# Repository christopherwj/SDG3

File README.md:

# SDG3 - Powered Speaker System - Happy Tunes

## What should I expect to find in this repo?

Here you can find all of the files related to Team 3's Senior Design Project

This includes: components, datasheets, simulations, source code and more!

## Who is on the team?

| Team Member         | Field               |
| :------------------ | :------------------ |
| Brian Ahlers        | Electrical Engineer |
| Abraham Carranza    | Computer Engineer   |
| Kaitlyn Hamiter     | Electrical Engineer |
| Christopher Johnson | Computer Engineer   |
| Christopher Kihano  | Computer Engineer   |

# Shortcuts

From here on you will find sections detailing different points of Team 3's progress, links to documents and Google Drive directories.

## Senior Design B

### Draw.io Diagrams

- <a href="https://drive.google.com/drive/folders/15kxVudf5h-fhxRucdEdU0__9-gUpvDf6?usp=sharing" target="_blank">Folder Directory</a>

### System Integration Testing
- [Report](https://docs.google.com/document/d/11B_BZgX_fD9LDzKS0TlejT2W-SY3xGZJBUBTwWxWOKQ/edit?usp=sharing)
- [Folder Directory](https://drive.google.com/drive/folders/19PX26QaqbOIaYj3eWc8ziYZd34B6GGTo?usp=sharing)

### Hardware Readiness

- [Report](https://docs.google.com/document/d/16WcHxM67mR_bLpcuLu_cNokmKFwlc5yR9lt_XE9QbTI/edit?usp=sharing)
- [Folder Directory](https://drive.google.com/drive/folders/1j9h-cdcIw9vPNtkVY1A0dE3LBrUp3cXq?usp=sharing)

### Firmware Readiness

- [Report](https://docs.google.com/document/d/1_yuX03Fo50LZgdDcOuhRRBqLqM6c0yxrTySWzuhtTM4/edit?usp=sharing)
- [Folder Directory](https://drive.google.com/drive/folders/1t-pBYhPXyJxyrI6B_gw4tiY_lfn7Jp15?usp=sharing)

### Team Labor Hours

- [Spreadsheet](https://docs.google.com/spreadsheets/d/12QhF0Mqp7NLQ3RBZjQvClqkk2QXMBvIy/edit?usp=sharing&ouid=104676273414826873055&rtpof=true&sd=true)
- [Folder Directory](https://drive.google.com/drive/folders/19Oa_INHHnQHptVcXvDggzD6vj_AUFLqU?usp=sharing)

## Senior Design A

### Draw.io Diagrams
- <a href="https://drive.google.com/drive/folders/15kxVudf5h-fhxRucdEdU0__9-gUpvDf6?usp=sharing" target="_blank">Folder Directory</a>

### System Description, Requirements, Validation

- [Report](https://docs.google.com/document/d/1fnrOCIRyJVDsxmta0oakdDbBKZW54d827w0m6OqQ11Q/edit?usp=sharing)
- [Folder Directory](https://drive.google.com/drive/folders/1NczNZ4O1j9Vx4oX85sgfJVTjJTQ-W3sH?usp=sharing)

### Risk Analysis

- [Report](https://drive.google.com/file/d/1sAik6q6ureZYssgTLGljBEHL8I2Zk15t/view?usp=sharing)
- [Folder Directory](https://drive.google.com/drive/folders/1NczNZ4O1j9Vx4oX85sgfJVTjJTQ-W3sH?usp=sharing)

### Prototype Activity

- [Report](https://drive.google.com/file/d/1stdICW6GUIWn7OOhUiIIFrHZ0VR0cqvk/view?usp=sharing)
- [Folder Directory](https://drive.google.com/drive/folders/1NczNZ4O1j9Vx4oX85sgfJVTjJTQ-W3sH?usp=sharing)

### Critical Design Review

- [Report](https://docs.google.com/presentation/d/1inkozGnM1z5_KCovr3mFNu3Ky42EYbz6ArtEo2gSImo/edit?usp=sharing)
- [Folder Directory](https://drive.google.com/drive/folders/1jWTyNvOkjsP8tEsv12XOycAalzhh8IQb?usp=sharing)

### Final Report

- [Report](https://docs.google.com/document/d/1AqZGzt35glmXr1-TCmBBXokeJKedO_IO3BRvOg3bReY/edit?usp=sharing)
- [Folder Directory](https://drive.google.com/drive/folders/1KJQUjUjOi4YFd6RUpi_W71EKjcTsQYTU?usp=sharing)

### Team Labor Hours

- [Spreadsheet](https://docs.google.com/spreadsheets/d/1y0pf061RG8TchD4RHMXZIr2CGgnv92BU/edit?usp=sharing&ouid=104676273414826873055&rtpof=true&sd=true)
- [Folder Directory](https://drive.google.com/drive/folders/1Dg6yo43kKn5nfYz5vgzlIPh3S6AtKxnr?usp=sharing)

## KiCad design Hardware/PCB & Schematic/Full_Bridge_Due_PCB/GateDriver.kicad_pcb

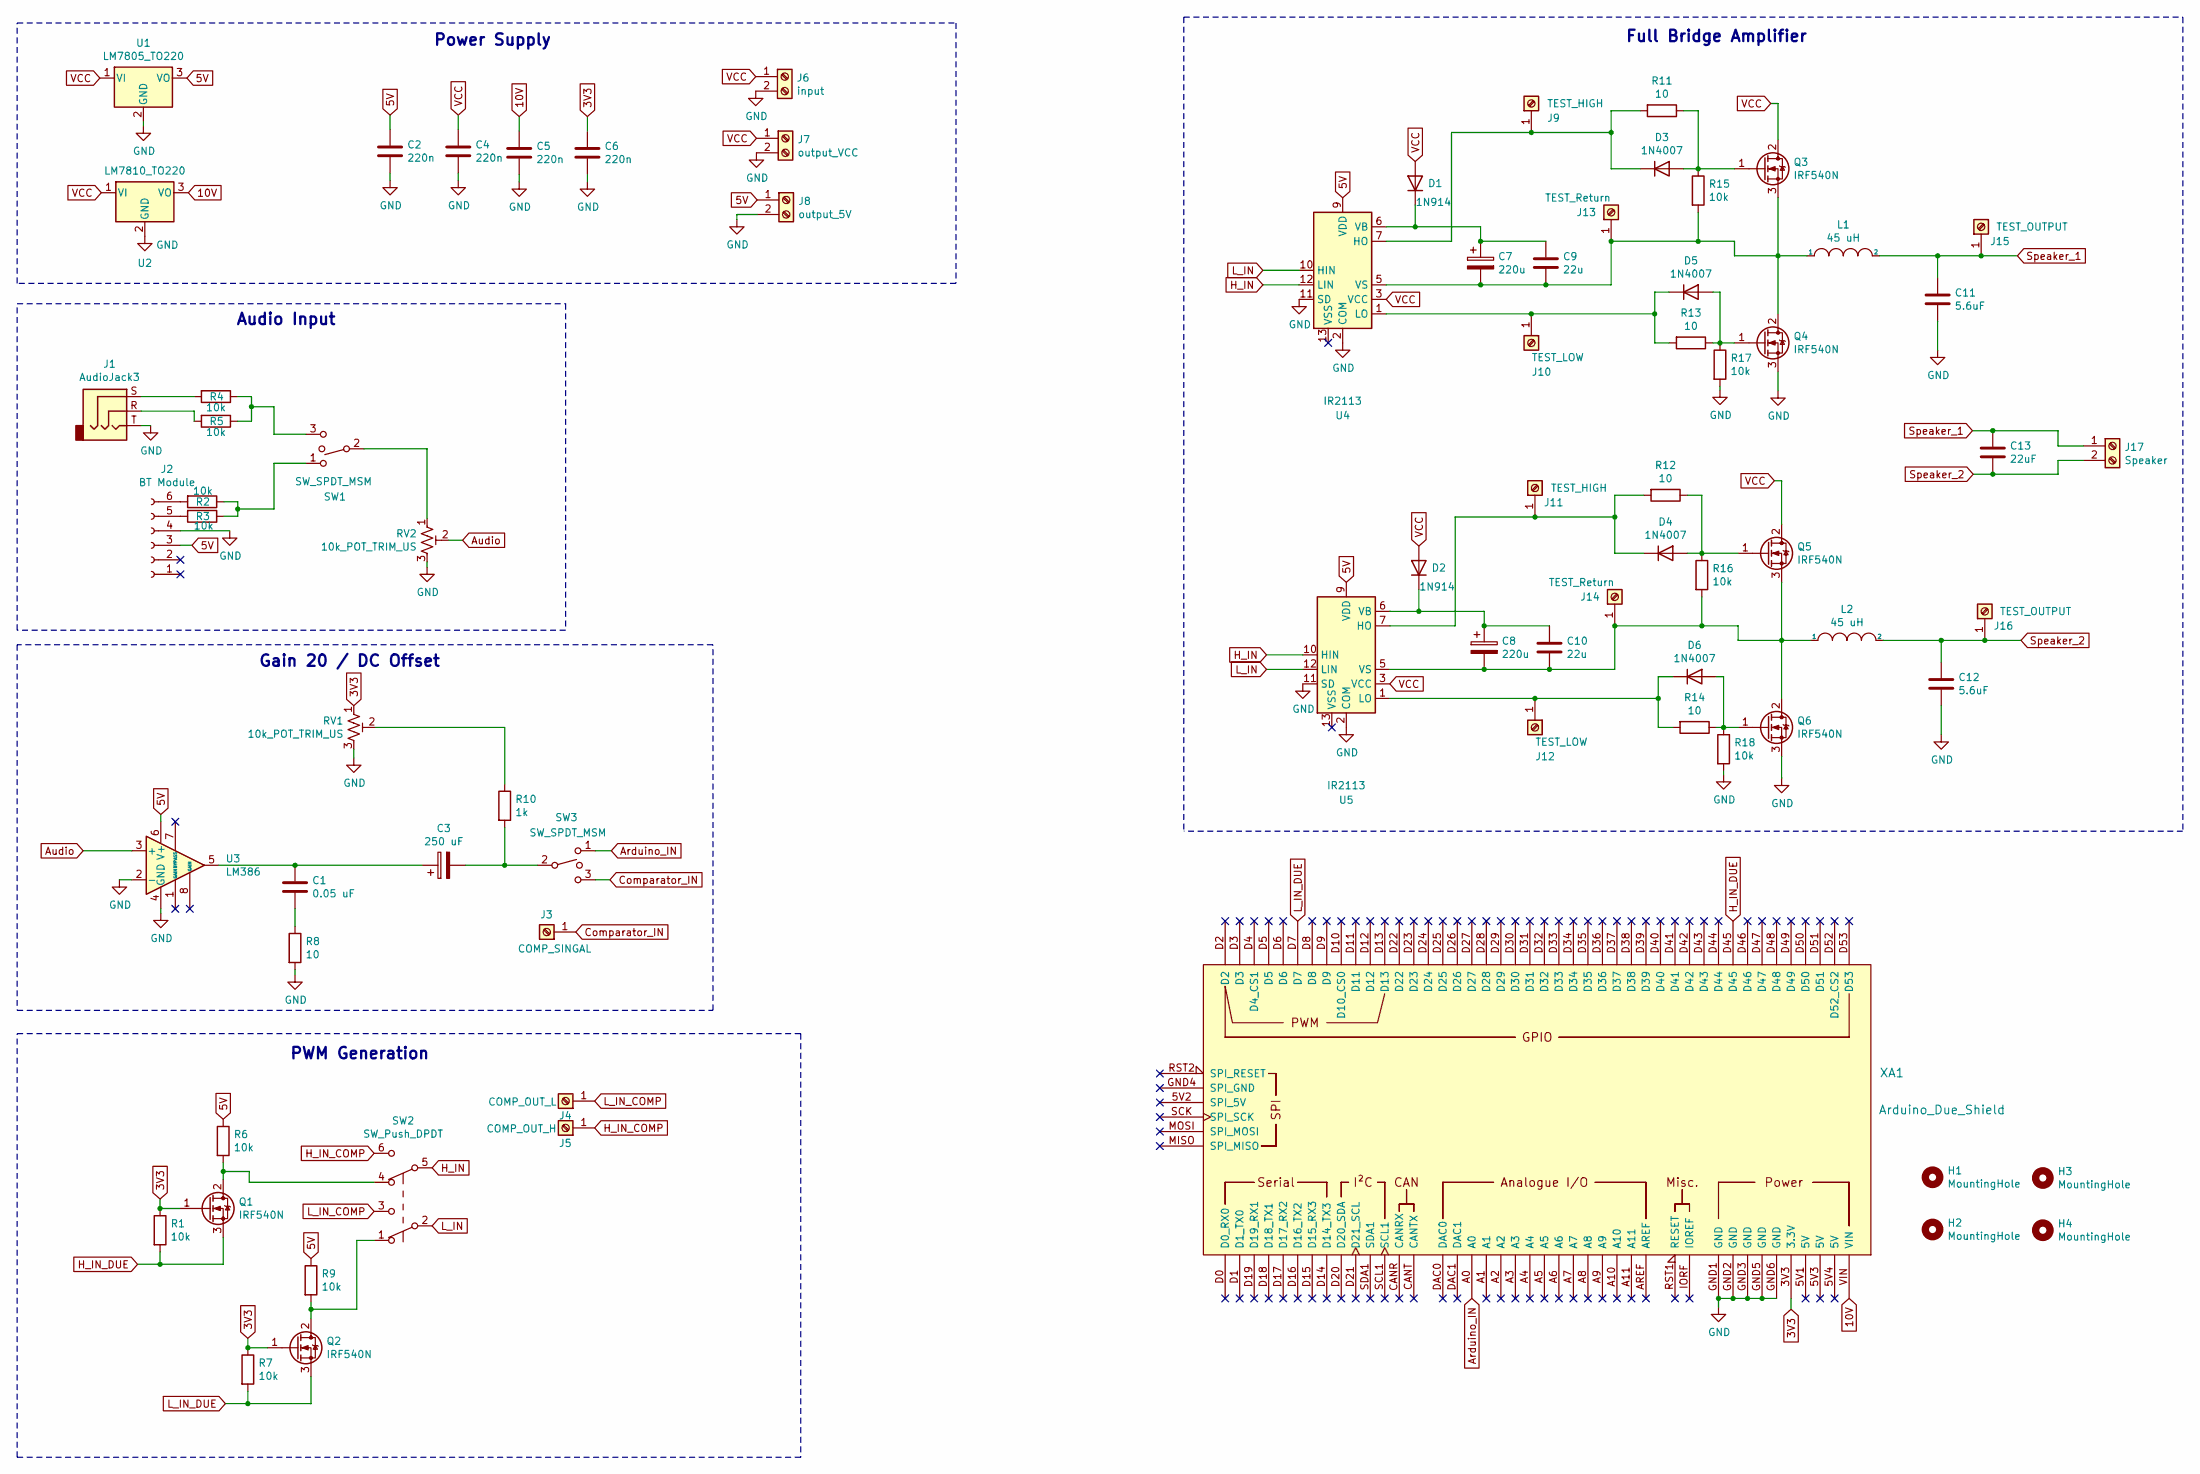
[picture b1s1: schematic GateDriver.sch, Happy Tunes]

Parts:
C1: 0.05 uF; C_Rect_L7.0mm_W2.5mm_P5.00mm
C2, C4, C5, C6: 220n; C_Rect_L7.0mm_W2.5mm_P5.00mm
C3: 250 uF; C_Rect_L7.0mm_W2.5mm_P5.00mm
C7, C8: 220u; C_Radial_D8.0mm_H7.0mm_P3.50mm
C9, C10: 22u; C_Rect_L7.0mm_W2.5mm_P5.00mm
C11, C12: 5.6uF; C_Rect_L7.0mm_W2.5mm_P5.00mm
C13: 22uF; C_Rect_L7.0mm_W2.5mm_P5.00mm
D1, D2: 1N914; D_DO-35_SOD27_P7.62mm_Horizontal
D3, D4, D5, D6: 1N4007; D_DO-41_SOD81_P10.16mm_Horizontal
H1, H2, H3, H4: MountingHole; MountingHole_2.2mm_M2
J1: AudioJack3; Jack_3.5mm_CUI_SJ1-3533NG_Horizontal
J2: BT Module; PinHeader_1x06_P2.54mm_Vertical
J3: COMP_SINGAL; Pin_D1.3mm_L11.0mm
J4: COMP_OUT_L; Pin_D1.3mm_L11.0mm
J5: COMP_OUT_H; Pin_D1.3mm_L11.0mm
J6: input; ScrewTerm
J7: output_VCC; ScrewTerm
J8: output_5V; ScrewTerm
J9, J11: TEST_HIGH; Pin_D1.3mm_L11.0mm
J10, J12: TEST_LOW; Pin_D1.3mm_L11.0mm
J13, J14: TEST_Return; Pin_D1.3mm_L11.0mm
J15, J16: TEST_OUTPUT; Pin_D1.3mm_L11.0mm
J17: Speaker; ScrewTerm
L1, L2: 45 uH; L_CommonMode_Toroid_Vertical_L24.0mm_W16.3mm_Px10.16mm_Py20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
Q1, Q2, Q3, Q4, Q5, Q6: IRF540N; TO-220-3_Vertical
R1, R2, R3, R4, R5, R6, R7, R9, R15, R16, R17, R18: 10k; R_Axial_DIN0204_L3.6mm_D1.6mm_P7.62mm_Horizontal
R8, R11, R12, R13, R14: 10; R_Axial_DIN0204_L3.6mm_D1.6mm_P7.62mm_Horizontal
R10: 1k; R_Axial_DIN0204_L3.6mm_D1.6mm_P7.62mm_Horizontal
RV1, RV2: 10k_POT_TRIM_US; Potentiometer_Alps_RK09K_Single_Horizontal
SW1, SW3: SW_SPDT_MSM; SW_CuK_OS102011MA1QN1_SPDT_Angled
SW2: SW_Push_DPDT; SW_CuK_JS202011AQN_DPDT_Angled
U1: LM7805_TO220; TO-220-3_Vertical
U2: LM7810_TO220; TO-220-3_Vertical
U3: LM386; DIP-8_W7.62mm_Socket
U4, U5: IR2113; DIP-14_W7.62mm_Socket
XA1: Arduino_Due_Shield

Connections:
3V3: C6.1, Q1.1 (G), Q2.1 (G), R1.1, R7.1, RV1.1, XA1.3V3 (3.3V)
5V: C2.1, J2.3, J8.1, R6.1, R9.1, U1.3 (VO), U3.6 (V+), U4.9 (VDD), U5.9 (VDD)
10V: C5.1, U2.3 (VO), XA1.VIN
Arduino_IN: SW3.1, XA1.A0
Audio: RV2.2, U3.3 (+)
Comparator_IN: J3.1, SW3.3
GND: C2.2, C4.2, C5.2, C6.2, C11.2, C12.2, J1.T, J2.4, J6.2, J7.2, J8.2, Q4.3 (S), Q6.3 (S), R8.2, R17.2, R18.2, RV1.3, RV2.3, U1.2 (GND), U2.2 (GND), U3.2 (-), U3.4 (GND), U4.2 (COM), U4.11 (SD), U5.2 (COM), U5.11 (SD), XA1.GND1 (GND), XA1.GND2 (GND), XA1.GND3 (GND), XA1.GND5 (GND), XA1.GND6 (GND)
H_IN: SW2.5 (B), U4.12 (LIN), U5.10 (HIN)
H_IN_COMP: J5.1, SW2.6 (C)
H_IN_DUE: Q1.3 (S), R1.2, XA1.D45
L_IN: SW2.2 (B), U4.10 (HIN), U5.12 (LIN)
L_IN_COMP: J4.1, SW2.3 (C)
L_IN_DUE: Q2.3 (S), R7.2, XA1.D7
unnamed: C1.1, C3.1, U3.5
unnamed: C1.2, R8.1
unnamed: C3.2, R10.2, SW3.2
unnamed: C7.1, C9.1, D1.1 (K), U4.6 (VB)
unnamed: C7.2, C9.2, J13.1, L1.1, Q3.3 (S), Q4.2 (D), R15.2, U4.5 (VS)
unnamed: C8.1, C10.1, D2.1 (K), U5.6 (VB)
unnamed: C8.2, C10.2, J14.1, L2.1, Q5.3 (S), Q6.2 (D), R16.2, U5.5 (VS)
unnamed: D3.1 (K), J9.1, R11.2, U4.7 (HO)
unnamed: D3.2 (A), Q3.1 (G), R11.1, R15.1
unnamed: D4.1 (K), J11.1, R12.2, U5.7 (HO)
unnamed: D4.2 (A), Q5.1 (G), R12.1, R16.1
unnamed: D5.1 (K), J10.1, R13.2, U4.1 (LO)
unnamed: D5.2 (A), Q4.1 (G), R13.1, R17.1
unnamed: D6.1 (K), J12.1, R14.2, U5.1 (LO)
unnamed: D6.2 (A), Q6.1 (G), R14.1, R18.1
unnamed: J1.R, R5.2
unnamed: J1.S, R4.2
unnamed: J2.5, R3.2
unnamed: J2.6, R2.2
unnamed: Q1.2 (D), R6.2, SW2.4 (A)
unnamed: Q2.2 (D), R9.2, SW2.1 (A)
unnamed: R2.1, R3.1, SW1.1
unnamed: R4.1, R5.1, SW1.3
unnamed: R10.1, RV1.2
unnamed: RV2.1, SW1.2
Speaker_1: C11.1, C13.1, J15.1, J17.1, L1.2
Speaker_2: C12.1, C13.2, J16.1, J17.2, L2.2
VCC: C4.1, D1.2 (A), D2.2 (A), J6.1, J7.1, Q3.2 (D), Q5.2 (D), U1.1 (VI), U2.1 (VI), U4.3 (VCC), U5.3 (VCC)

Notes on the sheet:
Audio Input
Gain 20 / DC Offset
Full Bridge Amplifier
Power Supply
PWM Generation

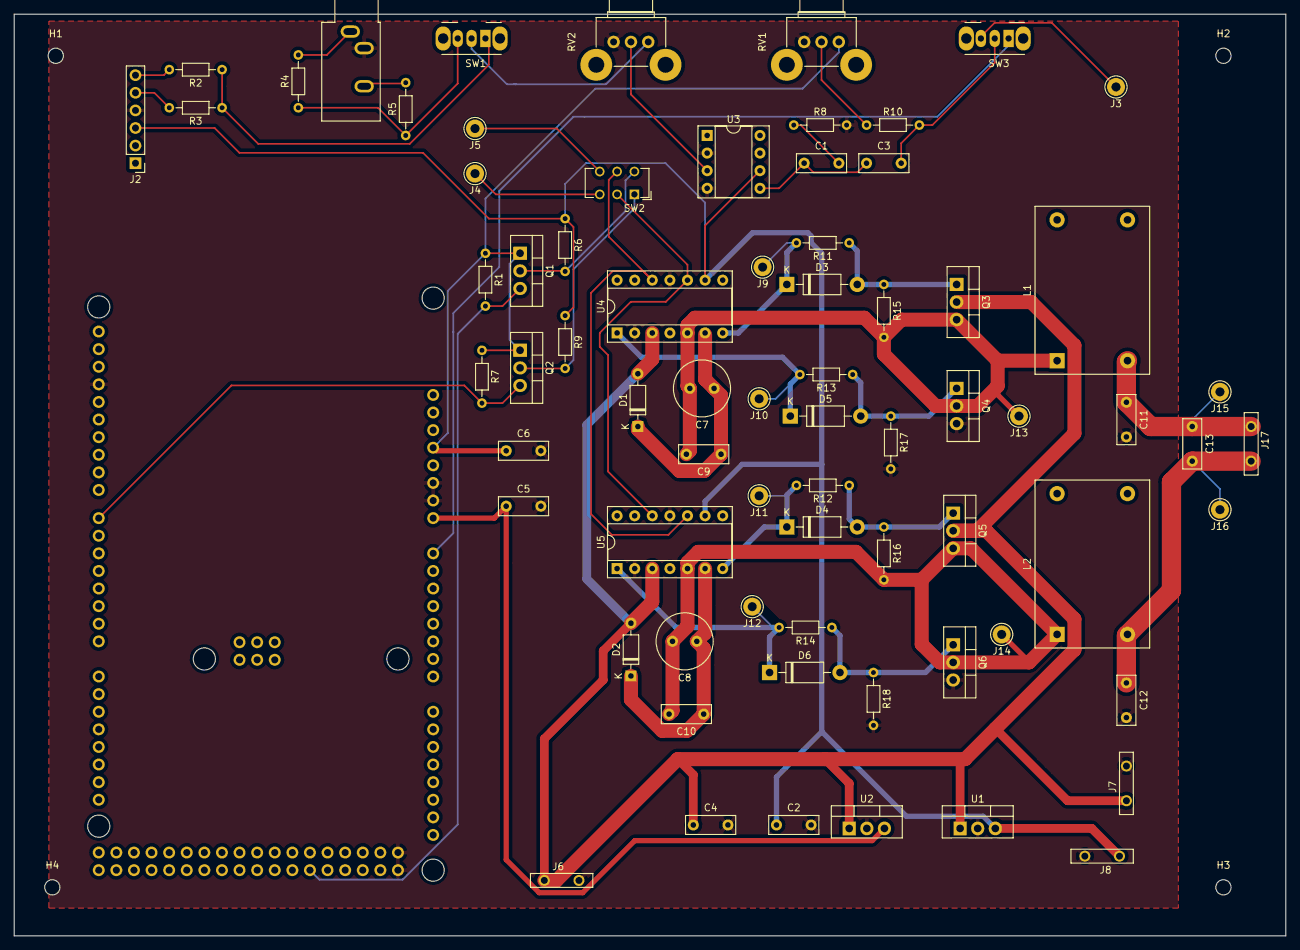
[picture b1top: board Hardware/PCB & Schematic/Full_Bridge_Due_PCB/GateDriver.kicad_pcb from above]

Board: 2 copper layers, 183.5 x 133.0 mm, 77 parts (1 on the bottom side), 41 nets.

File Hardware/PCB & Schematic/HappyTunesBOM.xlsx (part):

ref | value5 | footprint | datasheet | lib | part | description | names | tstamps6 | tstamp | lib7 | part8 | description9 | docs | fp | field | name10 | num | name11 | type | alias | logical | uri | code | name12 | ref13 | pin
C1 | 0.05 uF | Capacitor_THT:C_Rect_L7.0mm_W2.5mm_P5.00mm | ~ | Device | C | Unpolarized capacitor | / | / | 62162C29
C10 | 22u | Capacitor_THT:C_Rect_L7.0mm_W2.5mm_P5.00mm | ~ | Device | C | Unpolarized capacitor | / | / | 6213681C
C11 | 5.6uF | Capacitor_THT:C_Rect_L7.0mm_W2.5mm_P5.00mm | ~ | Device | C | Unpolarized capacitor | / | / | 61A5E88D
C12 | 5.6uF | Capacitor_THT:C_Rect_L7.0mm_W2.5mm_P5.00mm | ~ | Device | C | Unpolarized capacitor | / | / | 62136830
C13 | 22uF | Capacitor_THT:C_Rect_L7.0mm_W2.5mm_P5.00mm | ~ | Device | C | Unpolarized capacitor | / | / | 621D758A
C2 | 220n | Capacitor_THT:C_Rect_L7.0mm_W2.5mm_P5.00mm | ~ | Device | C | Unpolarized capacitor | / | / | 61AAA34E
C3 | 250 uF | Capacitor_THT:C_Rect_L7.0mm_W2.5mm_P5.00mm | ~ | Device | CP | Polarized capacitor | / | / | 62158BF0
C4 | 220n | Capacitor_THT:C_Rect_L7.0mm_W2.5mm_P5.00mm | ~ | Device | C | Unpolarized capacitor | / | / | 621A181D
C5 | 220n | Capacitor_THT:C_Rect_L7.0mm_W2.5mm_P5.00mm | ~ | Device | C | Unpolarized capacitor | / | / | 621C33C0
C6 | 220n | Capacitor_THT:C_Rect_L7.0mm_W2.5mm_P5.00mm | ~ | Device | C | Unpolarized capacitor | / | / | 621C33D6
C7 | 220u | Capacitor_THT:C_Radial_D8.0mm_H7.0mm_P3.50mm | ~ | Device | CP | Polarized capacitor | / | / | 6210F666
C8 | 220u | Capacitor_THT:C_Radial_D8.0mm_H7.0mm_P3.50mm | ~ | Device | CP | Polarized capacitor | / | / | 62136920
C9 | 22u | Capacitor_THT:C_Rect_L7.0mm_W2.5mm_P5.00mm | ~ | Device | C | Unpolarized capacitor | / | / | 61A5D009
D1 | 1N914 | Diode_THT:D_DO-35_SOD27_P7.62mm_Horizontal | http://www.vishay.com/docs/85622/1n914.pdf | Diode | 1N914 | 100V 0.3A Small Signal Fast Switching Diode, DO-35 | / | / | 62281C4C
D2 | 1N914 | Diode_THT:D_DO-35_SOD27_P7.62mm_Horizontal | http://www.vishay.com/docs/85622/1n914.pdf | Diode | 1N914 | 100V 0.3A Small Signal Fast Switching Diode, DO-35 | / | / | 621C6EB2
D3 | 1N4007 | Diode_THT:D_DO-41_SOD81_P10.16mm_Horizontal | http://www.vishay.com/docs/88503/1n4001.pdf | Diode | 1N4007 | 1000V 1A General Purpose Rectifier Diode, DO-41 | / | / | 61A569FB
D4 | 1N4007 | Diode_THT:D_DO-41_SOD81_P10.16mm_Horizontal | http://www.vishay.com/docs/88503/1n4001.pdf | Diode | 1N4007 | 1000V 1A General Purpose Rectifier Diode, DO-41 | / | / | 621367F4
D5 | 1N4007 | Diode_THT:D_DO-41_SOD81_P10.16mm_Horizontal | http://www.vishay.com/docs/88503/1n4001.pdf | Diode | 1N4007 | 1000V 1A General Purpose Rectifier Diode, DO-41 | / | / | 61A580C3
D6 | 1N4007 | Diode_THT:D_DO-41_SOD81_P10.16mm_Horizontal | http://www.vishay.com/docs/88503/1n4001.pdf | Diode | 1N4007 | 1000V 1A General Purpose Rectifier Diode, DO-41 | / | / | 621367FE
H1 | MountingHole | MountingHole:MountingHole_2.2mm_M2 | ~ | Mechanical | MountingHole | Mounting Hole without connection | / | / | 621DD05A
H2 | MountingHole | MountingHole:MountingHole_2.2mm_M2 | ~ | Mechanical | MountingHole | Mounting Hole without connection | / | / | 621EA6A0
H3 | MountingHole | MountingHole:MountingHole_2.2mm_M2 | ~ | Mechanical | MountingHole | Mounting Hole without connection | / | / | 621DEFD8
H4 | MountingHole | MountingHole:MountingHole_2.2mm_M2 | ~ | Mechanical | MountingHole | Mounting Hole without connection | / | / | 621EB10E
J1 | AudioJack3 | Connector_Audio:Jack_3.5mm_CUI_SJ1-3533NG_Horizontal | ~ | Connector | AudioJack3 | Audio Jack, 3 Poles (Stereo / TRS) | / | / | 623336F4
J10 | TEST_LOW | Connector_Pin:Pin_D1.3mm_L11.0mm | ~ | Connector | Screw_Terminal_01x01 | Generic screw terminal, single row, 01x01, script generated (kicad-library-util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 | / | / | 61F99901
J11 | TEST_HIGH | Connector_Pin:Pin_D1.3mm_L11.0mm | ~ | Connector | Screw_Terminal_01x01 | Generic screw terminal, single row, 01x01, script generated (kicad-library-util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 | / | / | 621368BD
J12 | TEST_LOW | Connector_Pin:Pin_D1.3mm_L11.0mm | ~ | Connector | Screw_Terminal_01x01 | Generic screw terminal, single row, 01x01, script generated (kicad-library-util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 | / | / | 621368C9
J13 | TEST_Return | Connector_Pin:Pin_D1.3mm_L11.0mm | ~ | Connector | Screw_Terminal_01x01 | Generic screw terminal, single row, 01x01, script generated (kicad-library-util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 | / | / | 61F9C69A
J14 | TEST_Return | Connector_Pin:Pin_D1.3mm_L11.0mm | ~ | Connector | Screw_Terminal_01x01 | Generic screw terminal, single row, 01x01, script generated (kicad-library-util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 | / | / | 621368E1
J15 | TEST_OUTPUT | Connector_Pin:Pin_D1.3mm_L11.0mm | ~ | Connector | Screw_Terminal_01x01 | Generic screw terminal, single row, 01x01, script generated (kicad-library-util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 | / | / | 61F9A94A
J16 | TEST_OUTPUT | Connector_Pin:Pin_D1.3mm_L11.0mm | ~ | Connector | Screw_Terminal_01x01 | Generic screw terminal, single row, 01x01, script generated (kicad-library-util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 | / | / | 621368D5
J17 | Speaker | CustomFootprints:ScrewTerm | ~ | Connector | Screw_Terminal_01x02 | Generic screw terminal, single row, 01x02, script generated (kicad-library-util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 | / | / | 621368A6
J2 | BT Module | Connector_PinHeader_2.54mm:PinHeader_1x06_P2.54mm_Vertical | ~ | Connector | Conn_01x06_Female | Generic connector, single row, 01x06, script generated (kicad-library-utils/sch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 | / | / | 6237F84A
J3 | COMP_SINGAL | Connector_Pin:Pin_D1.3mm_L11.0mm | ~ | Connector | Screw_Terminal_01x01 | Generic screw terminal, single row, 01x01, script generated (kicad-library-util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 | / | / | 62377881
J4 | COMP_OUT_L | Connector_Pin:Pin_D1.3mm_L11.0mm | ~ | Connector | Screw_Terminal_01x01 | Generic screw terminal, single row, 01x01, script generated (kicad-library-util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 | / | / | 6237E9E9
J5 | COMP_OUT_H | Connector_Pin:Pin_D1.3mm_L11.0mm | ~ | Connector | Screw_Terminal_01x01 | Generic screw terminal, single row, 01x01, script generated (kicad-library-util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 | / | / | 62381A12
J6 | input | CustomFootprints:ScrewTerm | ~ | Connector | Screw_Terminal_01x02 | Generic screw terminal, single row, 01x02, script generated (kicad-library-util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 | / | / | 61AA1413
J7 | output_VCC | CustomFootprints:ScrewTerm | ~ | Connector | Screw_Terminal_01x02 | Generic screw terminal, single row, 01x02, script generated (kicad-library-util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 | / | / | 61AB4357
J8 | output_5V | CustomFootprints:ScrewTerm | ~ | Connector | Screw_Terminal_01x02 | Generic screw terminal, single row, 01x02, script generated (kicad-library-util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 | / | / | 61AB4B41
J9 | TEST_HIGH | Connector_Pin:Pin_D1.3mm_L11.0mm | ~ | Connector | Screw_Terminal_01x01 | Generic screw terminal, single row, 01x01, script generated (kicad-library-util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 | / | / | 61F96EB2
L1 | 45 uH | Inductor_THT:L_CommonMode_Toroid_Vertical_L24.0mm_W16.3mm_Px10.16mm_Py20.32mm_m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 | ~ | pspice | INDUCTOR | Inductor symbol for simulation only | / | / | 61A5DF8E
L2 | 45 uH | Inductor_THT:L_CommonMode_Toroid_Vertical_L24.0mm_W16.3mm_Px10.16mm_Py20.32mm_m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 | https://www.murata-ps.com/pub/data/magnetics/kmp_3300.pdf | pspice | INDUCTOR | Inductor symbol for simulation only | / | / | 62136826
Q1 | IRF540N | Package_TO_SOT_THT:TO-220-3_Vertical | http://www.irf.com/product-info/datasheets/data/irf540n.pdf | Transistor_FET | IRF540N | 33A Id, 100V Vds, HEXFET N-Channel MOSFET, TO-220 | / | / | 62A0BE19
Q2 | IRF540N | Package_TO_SOT_THT:TO-220-3_Vertical | http://www.irf.com/product-info/datasheets/data/irf540n.pdf | Transistor_FET | IRF540N | 33A Id, 100V Vds, HEXFET N-Channel MOSFET, TO-220 | / | / | 62AE0A06
Q3 | IRF540N | Package_TO_SOT_THT:TO-220-3_Vertical | http://www.irf.com/product-info/datasheets/data/irf540n.pdf | Transistor_FET | IRF540N | 33A Id, 100V Vds, HEXFET N-Channel MOSFET, TO-220 | / | / | 61A7438A
Q4 | IRF540N | Package_TO_SOT_THT:TO-220-3_Vertical | http://www.irf.com/product-info/datasheets/data/irf540n.pdf | Transistor_FET | IRF540N | 33A Id, 100V Vds, HEXFET N-Channel MOSFET, TO-220 | / | / | 61A713D5
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
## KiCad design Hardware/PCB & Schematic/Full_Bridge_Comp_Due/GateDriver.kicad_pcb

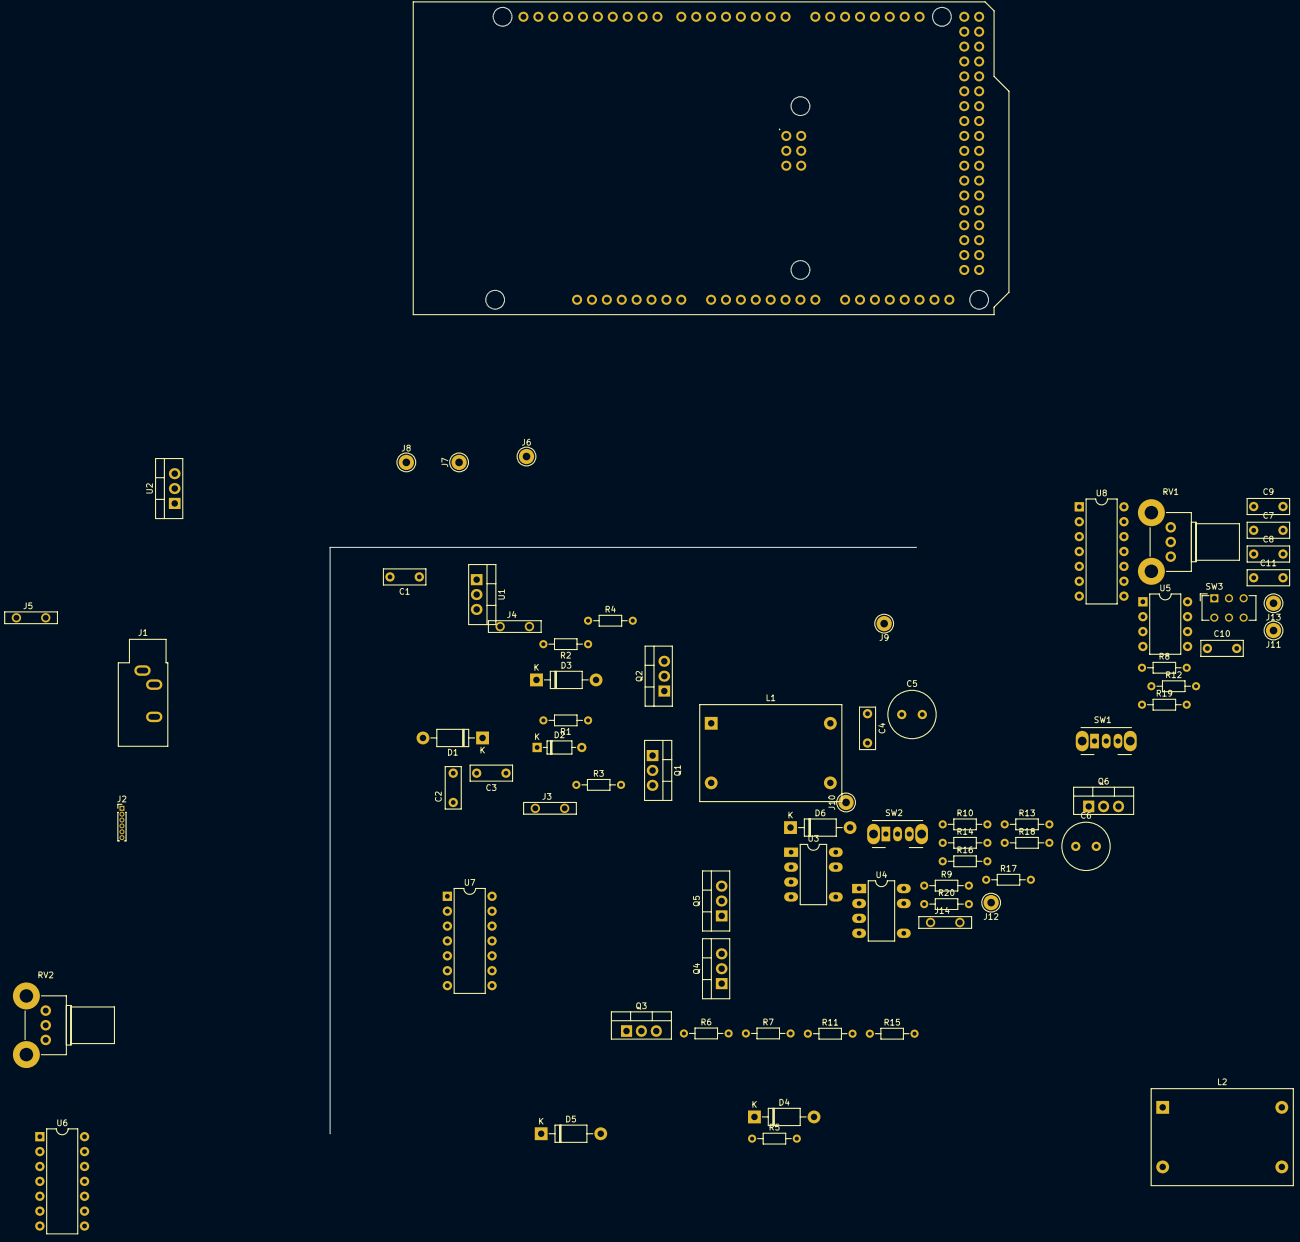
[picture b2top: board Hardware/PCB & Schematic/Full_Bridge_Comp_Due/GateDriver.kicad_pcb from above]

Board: 2 copper layers, 100.0 x 100.0 mm, 73 parts (0 on the bottom side), 43 nets, no tracks yet.

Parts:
C1: 1nF; C_Rect_L7.0mm_W2.5mm_P5.00mm
C2: 220n; C_Rect_L7.0mm_W2.5mm_P5.00mm
C3: 0.05 uF; C_Rect_L7.0mm_W2.5mm_P5.00mm
C4: 250 uF; C_Rect_L7.0mm_W2.5mm_P5.00mm
C5, C6: 220u; C_Radial_D8.0mm_H7.0mm_P3.50mm
C7, C8: 22u; C_Rect_L7.0mm_W2.5mm_P5.00mm
C9, C10: 5.6uF; C_Rect_L7.0mm_W2.5mm_P5.00mm
C11: 22uF; C_Rect_L7.0mm_W2.5mm_P5.00mm
D1, D3, D4, D5, D6: 1N4007; D_DO-41_SOD81_P10.16mm_Horizontal
D2: 1N914; D_DO-35_SOD27_P7.62mm_Horizontal
J1: AudioJack3; Jack_3.5mm_CUI_SJ1-3533NG_Horizontal
J2: BT Module; PinHeader_1x06_P1.00mm_Vertical
J3: input; ScrewTerm
J4: output_VCC; ScrewTerm
J5: output_5V; ScrewTerm
J6, J8: TEST_HIGH; Pin_D1.3mm_L11.0mm
J7, J9: TEST_LOW; Pin_D1.3mm_L11.0mm
J10, J11: TEST_Return; Pin_D1.3mm_L11.0mm
J12, J13: TEST_OUTPUT; Pin_D1.3mm_L11.0mm
J14: Speaker; ScrewTerm
L1, L2: 45 uH; L_CommonMode_Toroid_Vertical_L24.0mm_W16.3mm_Px10.16mm_Py20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
Q1, Q2, Q3, Q4, Q5, Q6: IRF540N; TO-220-3_Vertical
R1, R2, R3, R4, R8, R10, R11, R12, R17, R18, R19, R20: 10k; R_Axial_DIN0204_L3.6mm_D1.6mm_P7.62mm_Horizontal
R5, R9: 1k; R_Axial_DIN0204_L3.6mm_D1.6mm_P7.62mm_Horizontal
R6, R13, R14, R15, R16: 10; R_Axial_DIN0204_L3.6mm_D1.6mm_P7.62mm_Horizontal
R7: 2k; R_Axial_DIN0204_L3.6mm_D1.6mm_P7.62mm_Horizontal
RV1, RV2: 10k_POT_TRIM_US; Potentiometer_Alps_RK09K_Single_Horizontal
SW1, SW2: SW_SPDT_MSM; SW_CuK_OS102011MA1QN1_SPDT_Angled
SW3: SW_Push_DPDT; SW_CuK_JS202011AQN_DPDT_Angled
U1: LM7805_TO220; TO-220-3_Vertical
U2: LM7810_TO220; TO-220-3_Vertical
U3: LM386; PowerIntegrations_PDIP-8B
U4: LM393; PowerIntegrations_PDIP-8B
U5: LM555xN; DIP-8_W7.62mm
U6: 74AHC04; DIP-14_W7.62mm
U7, U8: IR2113; DIP-14_W7.62mm
XA1: Arduino_Due_Shield

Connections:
3V3: Q1.1, Q2.1, R8.1, R11.1, RV1.1, XA1.3V3
5V: C2.1, J2.3, J5.1, R5.1, R10.1, R12.1, U1.3, U4.8, U5.4, U5.8, U6.14, U7.9, U8.9
10V: U2.3, XA1.VIN
Arduino_IN: SW2.1, XA1.A0
Audio: RV2.2, U3.3
GND: C2.2, C9.2, C10.2, J1.T, J2.4, J3.2, J4.2, J5.2, Q4.3, Q6.3, R6.2, R19.2, R20.2, RV1.3, RV2.3, U1.2, U2.2, U3.2, U3.4, U4.4, U5.1, U6.7, U7.2, U7.11, U8.2, U8.11, XA1.GND1, XA1.GND2, XA1.GND3, XA1.GND5, XA1.GND6
H_IN_COMP: R5.2, SW3.6, U4.1, U6.1
H_IN_DUE: Q1.3, R8.2, XA1.D45
H_in: U7.12, U8.10
L_IN_COMP: SW3.3, U6.2
L_IN_DUE: Q2.3, R11.2, XA1.D7
L_in: U7.10, U8.12
unnamed: C1.2, R7.1, U5.2
unnamed: C3.1, C4.1, U3.5
unnamed: C3.2, R6.1
unnamed: C4.2, R9.2, SW2.2
unnamed: C5.1, C7.1, D1.1, U7.6
unnamed: C5.2, C7.2, J10.1, L1.1, Q3.3, Q4.2, R17.2, U7.5
unnamed: C6.1, C8.1, D2.1, U8.6
unnamed: C6.2, C8.2, J11.1, L2.1, Q5.3, Q6.2, R18.2, U8.5
unnamed: D3.1, J6.1, R13.2, U7.7
unnamed: D3.2, Q3.1, R13.1, R17.1
unnamed: D4.1, J8.1, R14.2, U8.7
unnamed: D4.2, Q5.1, R14.1, R18.1
unnamed: D5.1, J7.1, R15.2, U7.1
unnamed: D5.2, Q4.1, R15.1, R19.1
unnamed: D6.1, J9.1, R16.2, U8.1
unnamed: D6.2, Q6.1, R16.1, R20.1
unnamed: J1.R, R4.2
unnamed: J1.S, R3.2
unnamed: J2.5, R2.2
unnamed: J2.6, R1.2
unnamed: Q1.2, R10.2, SW3.4
unnamed: Q2.2, R12.2, SW3.1
unnamed: R1.1, R2.1, SW1.1
unnamed: R3.1, R4.1, SW1.3
unnamed: R7.2, U5.3, U5.6
unnamed: R9.1, RV1.2
unnamed: RV2.1, SW1.2
Speaker_1: C9.1, C11.1, J12.1, J14.1, L1.2
Speaker_2: C10.1, C11.2, J13.1, J14.2, L2.2
Triangle: C1.1, U4.2
VCC: D1.2, D2.2, J3.1, J4.1, Q3.2, Q5.2, U1.1, U2.1, U7.3, U8.3

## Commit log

2021-10-22 adding IR2011 Files
2021-10-26 Added files for allAboutCircuits
2021-10-26 Added rough draft comparator circuit
2021-10-26 Added LM339 Comparator to ltSpiceComponents
2021-10-26 resister value changed 10000->10k
    changed resistor values to be easier to read and less confusing
2021-10-27 Added pinout diagram
2021-11-01 Added schematics for 555 timer
2021-11-06 Added block diagram example
2021-11-06 12V 5V Circuit Simulation
    Complete Circuit is non functional too complex sub circuits functional
2021-11-10 Create Class_D_Amplifier_prototype_SDG3.pdf
    Changed Schematic to be more accurate with the author
2021-11-10 Adding scope captures
    Added scope captures from 11/8/2021 for Chris and Brian
2021-11-10 Added datasheet for IR2011 driver
2021-11-10 Removed old simulation added new ones
    Added LTSpice simulation for class D amplifier. Removed old LTSpice files on main.
2021-11-11 Updated Sim and Hardware for report
2022-01-21 Create main.cpp
    PWM Tester for Due
2022-01-21 Added ADC functionality, fixed garbage serial input bug
    We may need to tweak the ADC sample frequency, I can't tell without lab equipment if it's set to a high enough frequency for audio.
    I've tested the ADC in with PWM out functionality using a potentiometer and LEDs and it's working as intended and demonstratable.
    serial garbage issue was when the Due would restart/reset, there would be garbage in the input buffer which would trigger the response to show the Amplitude/Deadtime output string but as garbled mess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
2022-01-22 Dynamic serial interface enable.
    Forgot my plan to initially use analog inputs unless there's a serial command.
2022-01-24 PWM Interrupt flag wasn't cleared
    This bug didn't show up til the last change I made and didn't test it before I pushed the change. I forgot to clear the status flag on the PWM interrupt. If forgotten, the PWM interrupt repeats witho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
2022-01-25 Rename main.cpp to main.ino
    So it opens in Arduino IDE.
2022-01-28 Added some function descriptions
2022-02-11 Changed Stylized DEFINES to be more easily read
    I made no structural or function changes to the code. I changed the
    pound defines to be more easily read by have underscores between words
    so the code is more easily read.
2022-02-23 Updates
    - Created, updated, and deleted directories to appropriately organize files related to Happy Tunes
    - Updated README.md in repo root
    - Renamed several files to improve representation of their contents
    - Included .gitignore
2022-02-23 Created 3 Markdown files
    - Details contents of directory and it's redirections
2022-02-24 Removed Nested README Files and Updated Top README
2022-02-28 Hardware Readiness Material
    All items used within hardware readiness. Hardware 3d models created in Solidworks, PCB & Schematic within Hardware and LTSpice Simulations of Gate driver and level shifter
2022-03-17 Adding links for System Integration
2022-03-30 Initial Commit
    Untested, moving code from testing file to actual firmware.
2022-04-08 Updated file structure to use with VSCode
2022-04-24 Current updates
2022-04-24 Added mapRange, rollingAverage, changed ranges of inputs.
    mapRange uses floating point math to map one range onto another. rollingAverage takes the last N many samples and averages them together to smooth out spikes.
    Changed the mapping ranges to amplify the ranges we'll be reading.
2022-04-29 Firmware with 10kHz filter
    Lots of debug code still here, will remove in next iteration.
